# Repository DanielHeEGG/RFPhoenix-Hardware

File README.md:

# RF Phoenix
Open source wireless igniter for amateur rocketry

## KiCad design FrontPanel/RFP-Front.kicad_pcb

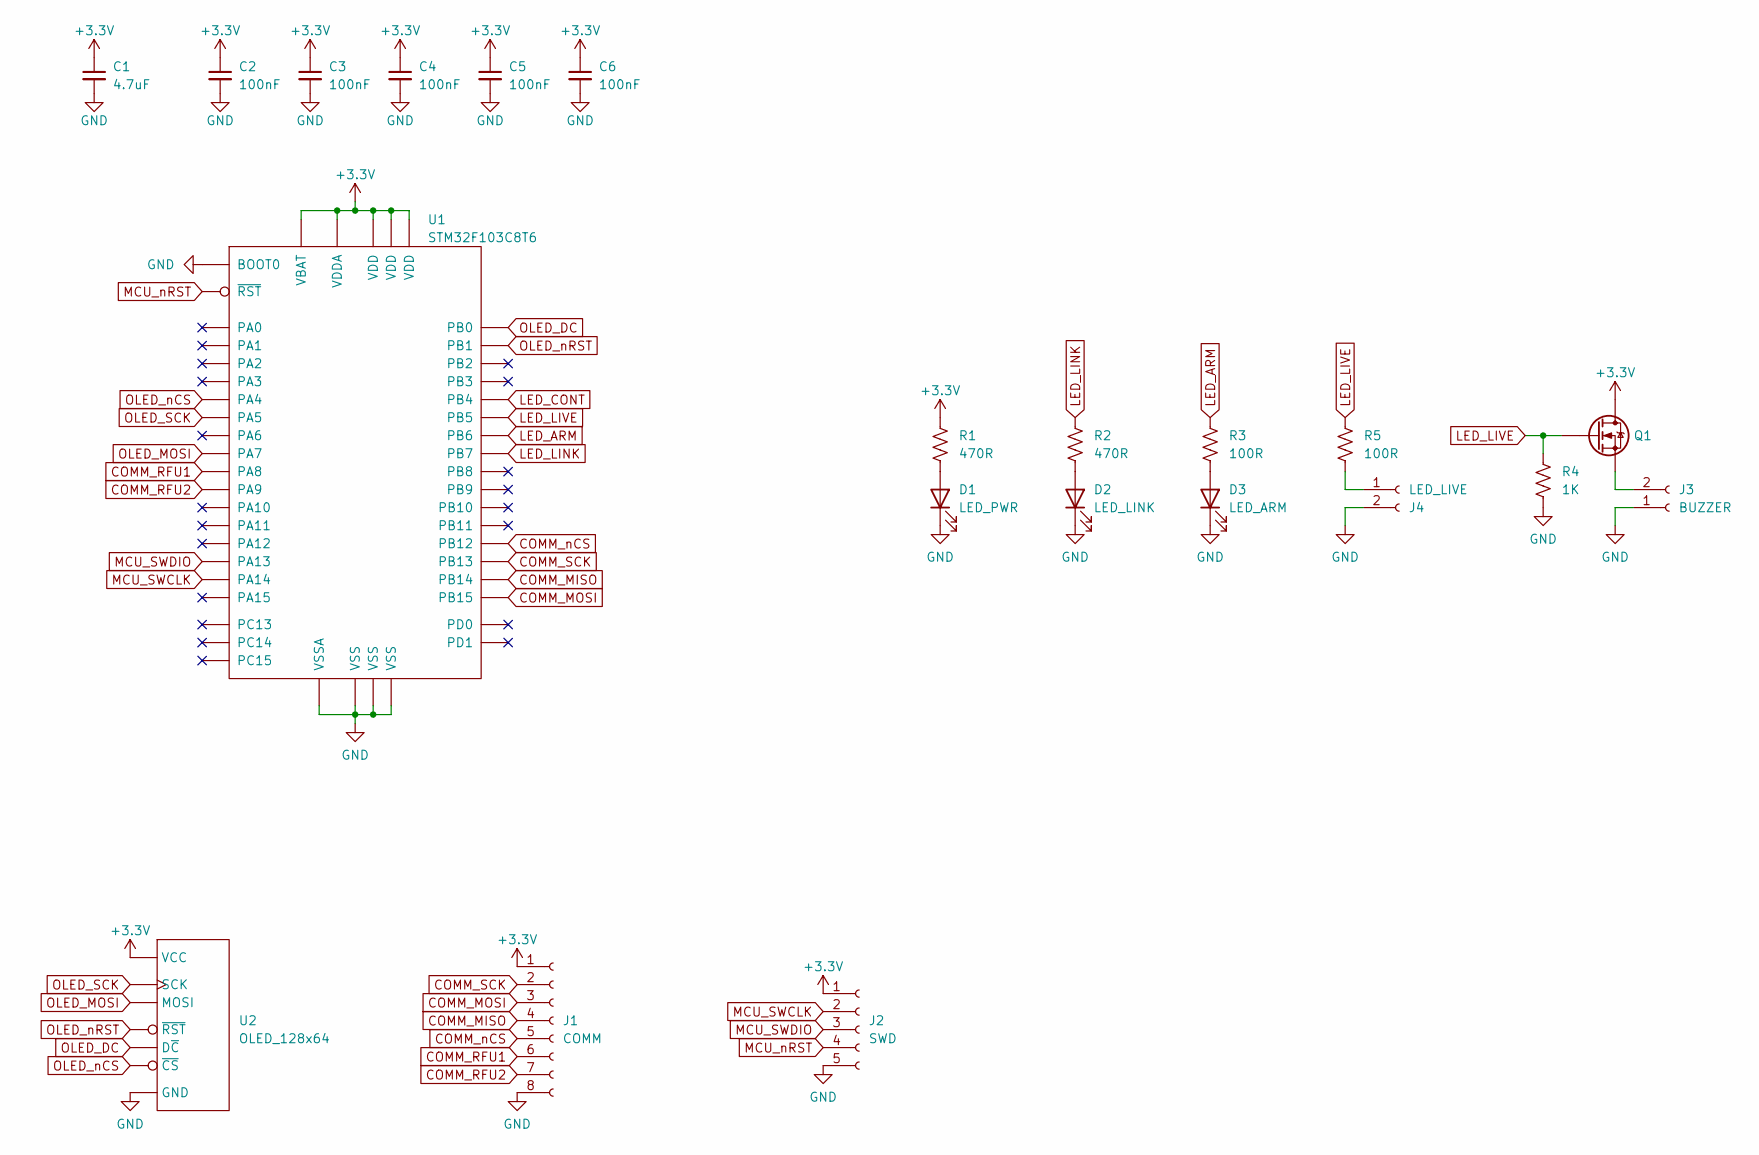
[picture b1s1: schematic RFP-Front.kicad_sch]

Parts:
C1: 4.7uF; C_0603_1608Metric; Part# Generic 4.7uF 6.3V 0603 X7R MLCC
C2, C3, C4, C5, C6: 100nF; C_0402_1005Metric; Part# Generic 100nF 6.3V 0402 X7R MLCC
D1: LED_PWR; LED_0603_1608Metric; Part# Generic Red 0603 LED
D2: LED_LINK; LED_0603_1608Metric; Part# Generic Green 0603 LED
D3: LED_ARM; LED_0603_1608Metric; Part# Generic Red 0603 LED
J1: COMM; Hirose_DF52-8S-0.8H_1x08-1MP_P0.80mm_Horizontal; Part# DF52-8S-0.8H
J2: SWD; Hirose_DF52-5S-0.8H_1x05-1MP_P0.80mm_Horizontal; Part# DF52-5S-0.8H
J3: BUZZER; Buzzer_Murata_PKMCS0909E
J4: LED_LIVE; R_2512_6332Metric
Q1: SOT-23; Part# Generic SOT-23 N-MOSFET
R1, R2: 470R; R_0402_1005Metric; Part# Generic 470R 0402 Resistor
R3, R5: 100R; R_0402_1005Metric; Part# Generic 100R 0402 Resistor
R4: 1K; R_0402_1005Metric; Part# Generic 1K 0402 Resistor
U1: STM32F103C8T6; LQFP-48_7x7mm_P0.5mm; Part# STM32F103C8T6
U2: OLED_128x64

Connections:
+3.3V: C1.1, C2.1, C3.1, C4.1, C5.1, C6.1, J1.1, J2.1, Q1.3 (D), R1.1, U1.1 (VBAT), U1.9 (VDDA), U1.24 (VDD), U1.36 (VDD), U1.48 (VDD), U2.2 (VCC)
COMM_MISO: J1.4, U1.27 (PB14)
COMM_MOSI: J1.3, U1.28 (PB15)
COMM_RFU1: J1.6, U1.29 (PA8)
COMM_RFU2: J1.7, U1.30 (PA9)
COMM_SCK: J1.2, U1.26 (PB13)
COMM_nCS: J1.5, U1.25 (PB12)
GND: C1.2, C2.2, C3.2, C4.2, C5.2, C6.2, D1.1 (K), D2.1 (K), D3.1 (K), J1.8, J2.5, J3.1, J4.2, R4.2, U1.8 (VSSA), U1.23 (VSS), U1.35 (VSS), U1.44 (BOOT0), U1.47 (VSS), U2.1 (GND)
LED_ARM: R3.1, U1.42 (PB6)
LED_CONT: U1.40 (PB4)
LED_LINK: R2.1, U1.43 (PB7)
LED_LIVE: Q1.1 (G), R4.1, R5.1, U1.41 (PB5)
MCU_SWCLK: J2.2, U1.37 (PA14)
MCU_SWDIO: J2.3, U1.34 (PA13)
MCU_nRST: J2.4, U1.7 (~RST)
unnamed: D1.2 (A), R1.2
unnamed: D2.2 (A), R2.2
unnamed: D3.2 (A), R3.2
unnamed: J3.2, Q1.2 (S)
unnamed: J4.1, R5.2
OLED_DC: U1.18 (PB0), U2.6 (D~C)
OLED_MOSI: U1.17 (PA7), U2.4 (MOSI)
OLED_SCK: U1.15 (PA5), U2.3 (SCK)
OLED_nCS: U1.14 (PA4), U2.7 (~CS)
OLED_nRST: U1.19 (PB1), U2.5 (~RST)

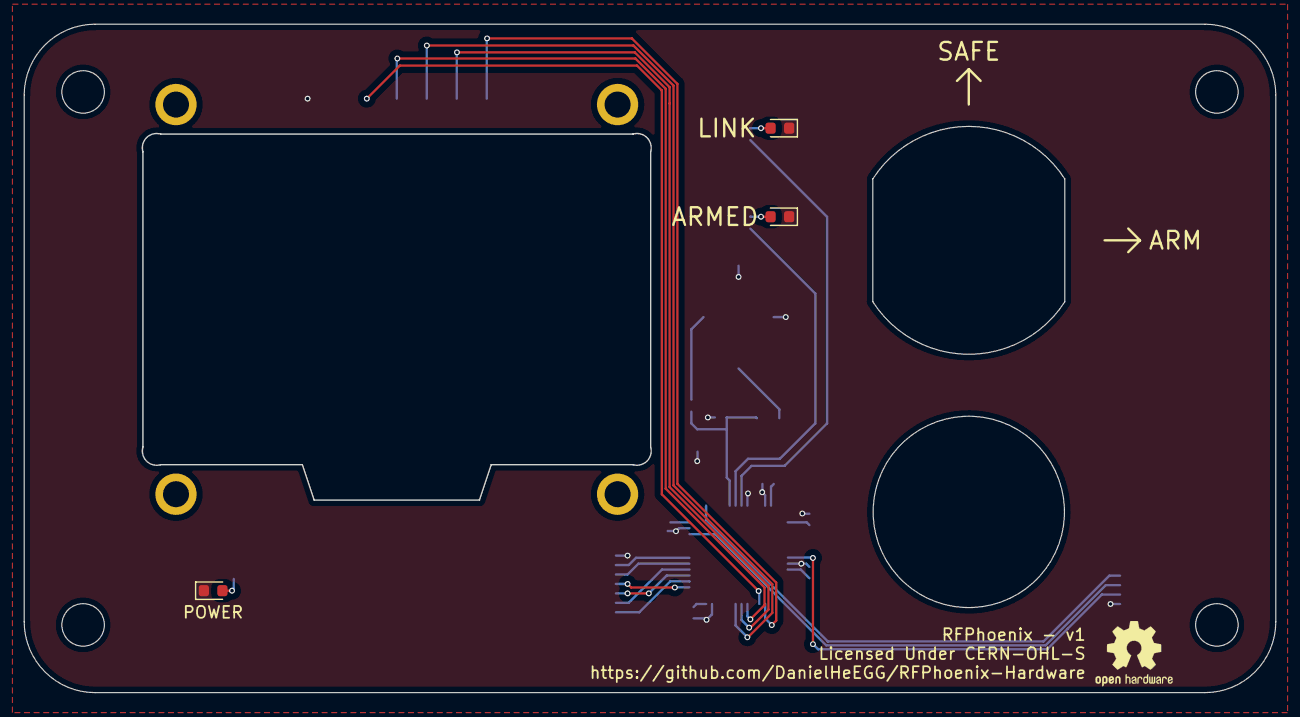
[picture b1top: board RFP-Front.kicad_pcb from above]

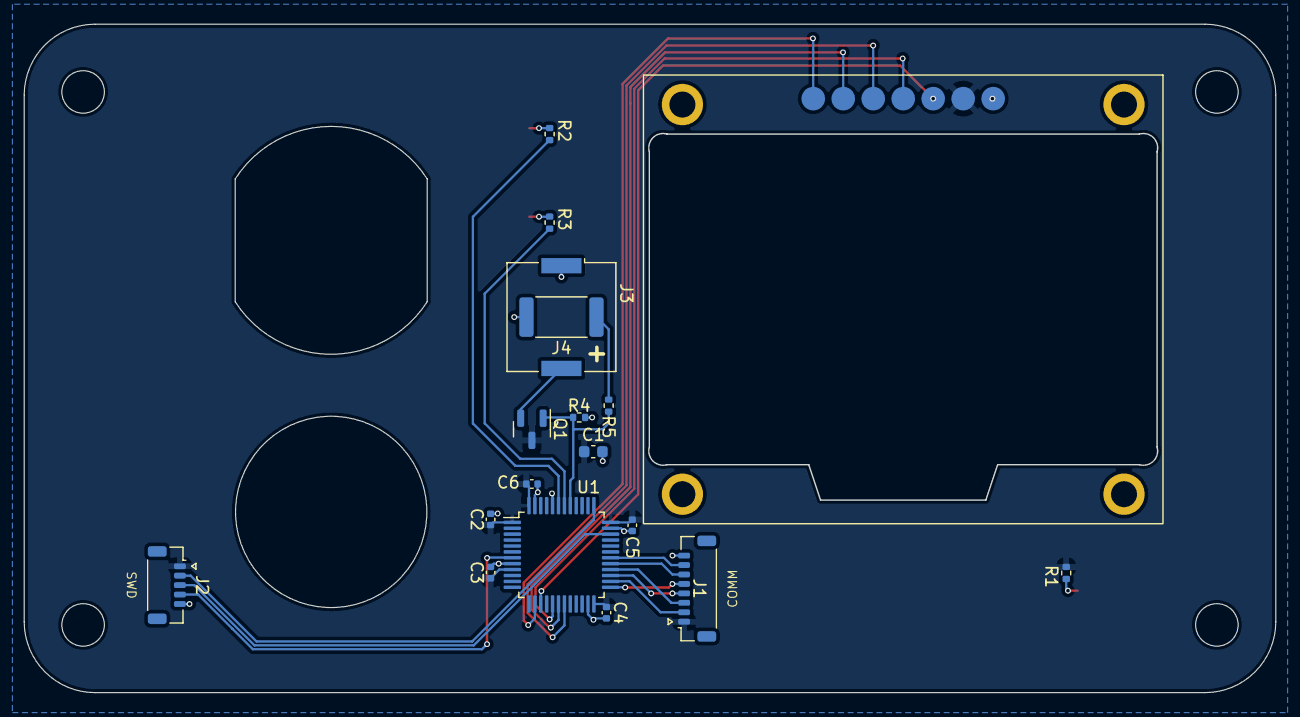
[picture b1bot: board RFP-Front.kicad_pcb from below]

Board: 2 copper layers, 106.0 x 56.6 mm, 21 parts (17 on the bottom side), 24 nets.

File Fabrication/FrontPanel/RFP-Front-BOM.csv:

"Qty","Designator","Comment","Footprint","Manufacturer","Part#","LCSC"
"1","C1","4.7uF","Capacitor_SMD:C_0603_1608Metric","Generic","Generic 4.7uF 6.3V 0603 X7R MLCC"
"5","C2, C3, C4, C5, C6","100nF","Capacitor_SMD:C_0402_1005Metric","Generic","Generic 100nF 6.3V 0402 X7R MLCC"
"1","D1","LED_PWR","LED_SMD:LED_0603_1608Metric","Generic","Generic Red 0603 LED","C2286"
"1","D2","LED_LINK","LED_SMD:LED_0603_1608Metric","Generic","Generic Green 0603 LED","C72043"
"1","D3","LED_ARM","LED_SMD:LED_0603_1608Metric","Generic","Generic Red 0603 LED","C2286"
"1","J1","DF52-8S-0.8H","Connector_Hirose:Hirose_DF52-8S-0.8H_1x08-1MP_P0.80mm_Horizontal","Hirose","DF52-8S-0.8H","C506726"
"1","J2","DF52-5S-0.8H","Connector_Hirose:Hirose_DF52-5S-0.8H_1x05-1MP_P0.80mm_Horizontal","Hirose","DF52-5S-0.8H","C597949"
"1","Q1","~","Package_TO_SOT_SMD:SOT-23","Generic","Generic SOT-23 N-MOSFET","C347475"
"2","R1, R2","470R","Resistor_SMD:R_0402_1005Metric","Generic","Generic 470R 0402 Resistor"
"2","R3, R5","100R","Resistor_SMD:R_0402_1005Metric","Generic","Generic 100R 0402 Resistor"
"1","R4","1K","Resistor_SMD:R_0402_1005Metric","Generic","Generic 1K 0402 Resistor"
"1","U1","STM32F103C8T6","Package_QFP:LQFP-48_7x7mm_P0.5mm","ST","STM32F103C8T6"

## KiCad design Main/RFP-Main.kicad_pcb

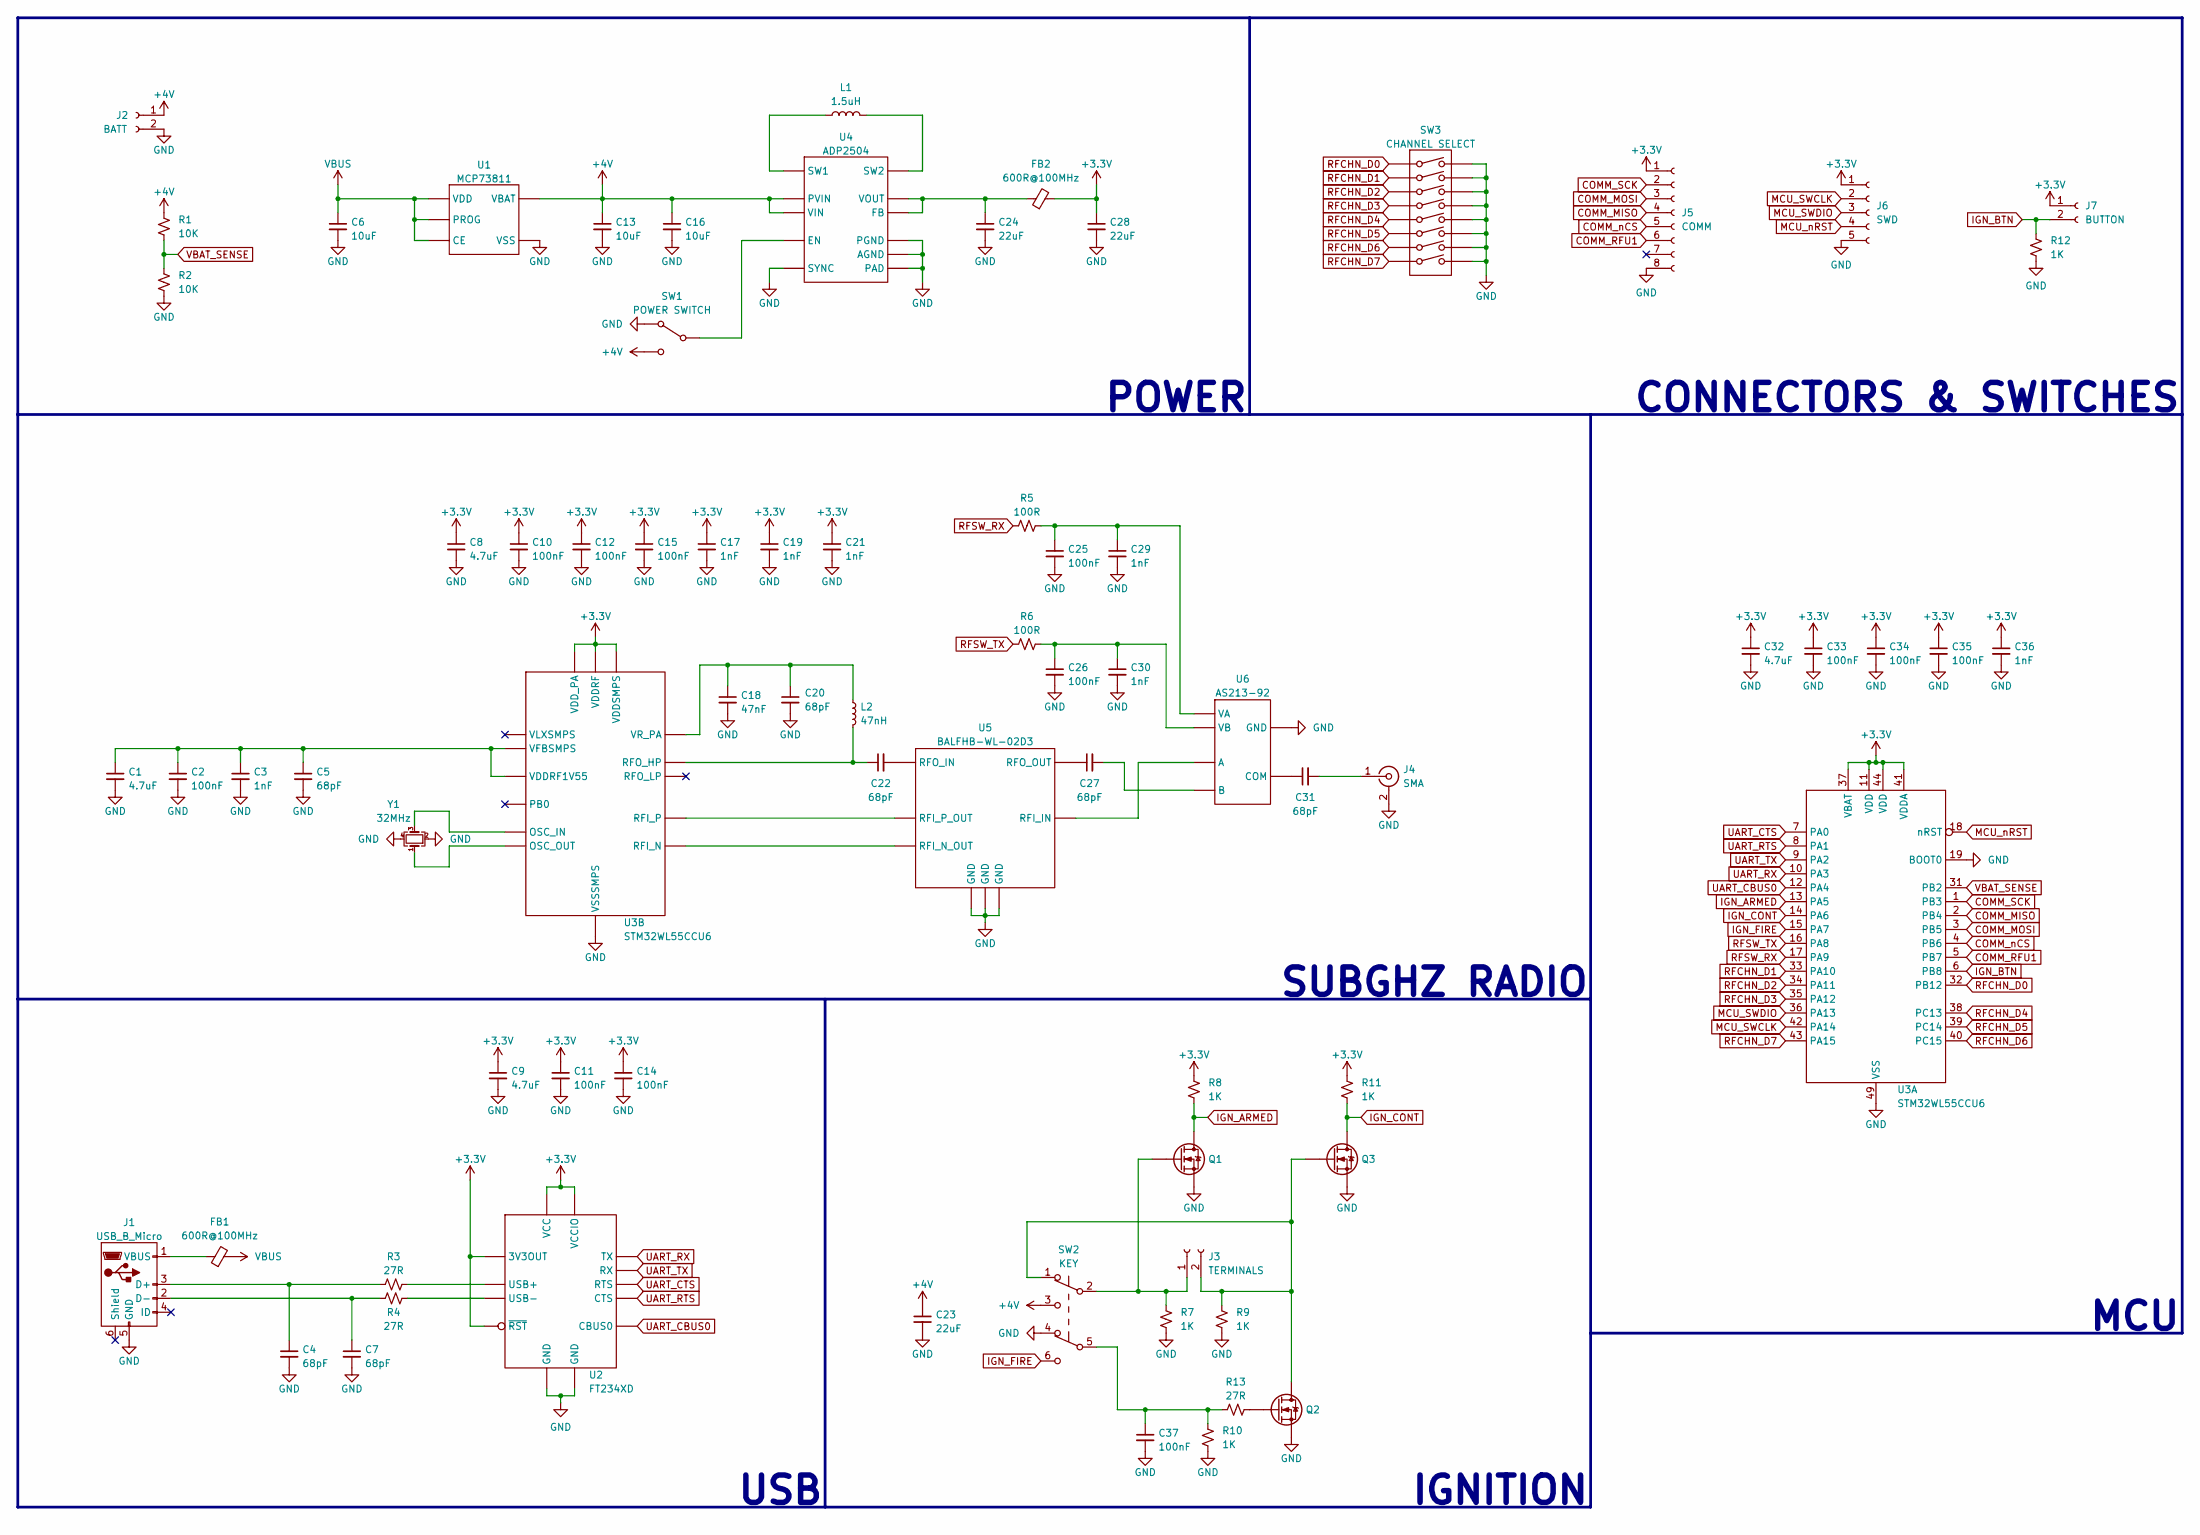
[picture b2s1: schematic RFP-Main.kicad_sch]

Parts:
C1, C8, C9, C32: 4.7uF; C_0603_1608Metric; Part# Generic 4.7uF 6.3V 0603 X7R MLCC
C2, C10, C11, C12, C14, C15, C25, C26, C33, C34, C35, C37: 100nF; C_0402_1005Metric; Part# Generic 100nF 6.3V 0402 X7R MLCC
C3, C17, C19, C21, C29, C30, C36: 1nF; C_0201_0603Metric; Part# Generic 1nF 6.3V 0201 X7R MLCC
C4, C5, C7, C20, C22, C27, C31: 68pF; C_0201_0603Metric; Part# GRM0335C1H680JA01D
C6, C13, C16: 10uF; C_0805_2012Metric; Part# Generic 10uF 6.3V 0805 X7R MLCC
C18: 47nF; C_0402_1005Metric; Part# Generic 47nF 6.3V 0402 X7R MLCC
C23, C24, C28: 22uF; C_0805_2012Metric; Part# Generic 22uF 6.3V 0805 X7R MLCC
FB1, FB2: 600R@100MHz; R_1206_3216Metric; Part# MH3261-601Y
J1: USB_B_Micro; USB_Micro-B_Molex-105017-0001; Part# 1050170001
J2: BATT; PinSocket_1x02_P2.54mm_Vertical
J3: TERMINALS; PinSocket_1x02_P2.54mm_Vertical
J4: SMA; SMA_Molex_73251-2200_Horizontal; Part# 0732512200
J5: COMM; Hirose_DF52-8S-0.8H_1x08-1MP_P0.80mm_Horizontal; Part# DF52-8S-0.8H
J6: SWD; Hirose_DF52-5S-0.8H_1x05-1MP_P0.80mm_Horizontal; Part# DF52-5S-0.8H
J7: BUTTON; PinSocket_1x02_P2.54mm_Vertical
L1: 1.5uH; L_1008_2520Metric; Part# LQM2HPN1R5MG0L
L2: 47nH; L_0402_1005Metric; Part# LQW15AN47NG00D
Q1, Q2, Q3: SOT-523; Part# DMG1012T
R1, R2: 10K; R_0402_1005Metric; Part# Generic 10K 0.1% 0402 Resistor
R3, R4, R13: 27R; R_0201_0603Metric; Part# Generic 27R 0201 Resistor
R5, R6: 100R; R_0402_1005Metric; Part# Generic 100R 0402 Resistor
R7, R8, R9, R10, R11, R12: 1K; R_0402_1005Metric; Part# Generic 1K 0402 Resistor
SW1: POWER SWITCH; SW_E-Switch_EG1224_SPDT_Angled; Part# EG1224
SW2: KEY; PinSocket_1x06_P2.54mm_Vertical
SW3: CHANNEL SELECT; SW_DIP_SPSTx08_Slide_6.7x21.88mm_W6.73mm_P2.54mm_LowProfile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; Part# 219-8LPSTR
U1: MCP73811; SOT-23-5; Part# MCP73811T-420I/OT
U2: FT234XD; DFN-12-1EP_3x3mm_P0.5mm_EP1.6x2.5mm; Part# FT234XD-R
U3: STM32WL55CCU6; QFN-48-1EP_7x7mm_P0.5mm_EP5.6x5.6mm; Part# STM32WL55CCU6
U4: ADP2504; LFCSP-WD-10-1EP_3x3mm_P0.5mm_EP1.64x2.38mm; Part# ADP2504ACPZ-3.3-R7
U5: BALFHB-WL-02D3; ST_CSPG-8; Part# BALFHB-WL-02D3
U6: AS213-92; SOT-363_SC-70-6; Part# AS213-92LF
Y1: 32MHz; Crystal_SMD_2016-4Pin_2.0x1.6mm; Part# NX2016SA-32M-EXS00A-CS06465

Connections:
+3.3V: C8.1, C9.1, C10.1, C11.1, C12.1, C14.1, C15.1, C17.1, C19.1, C21.1, C28.1, C32.1, C33.1, C34.1, C35.1, C36.1, FB2.2, J5.1, J6.1, J7.1, R8.1, R11.1, U2.2 (~RST), U2.3 (3V3OUT), U2.4 (VCC), U2.9 (VCCIO), U3.11 (VDD), U3.25 (VDD_PA), U3.28 (VDDRF), U3.37 (VBAT), U3.41 (VDDA), U3.44 (VDD), U3.46 (VDDSMPS)
+4V: C13.1, C16.1, C23.1, J2.1, R1.1, SW1.3 (C), SW2.3 (C), U1.3 (VBAT), U4.5 (PVIN), U4.8 (VIN)
COMM_MISO: J5.4, U3.2 (PB4)
COMM_MOSI: J5.3, U3.3 (PB5)
COMM_RFU1: J5.6, U3.5 (PB7)
COMM_SCK: J5.2, U3.1 (PB3)
COMM_nCS: J5.5, U3.4 (PB6)
GND: C1.2, C2.2, C3.2, C4.2, C5.2, C6.2, C7.2, C8.2, C9.2, C10.2, C11.2, C12.2, C13.2, C14.2, C15.2, C16.2, C17.2, C18.2, C19.2, C20.2, C21.2, C23.2, C24.2, C25.2, C26.2, C28.2, C29.2, C30.2, C32.2, C33.2, C34.2, C35.2, C36.2, C37.2, J1.5 (GND), J2.2, J4.2 (Ext), J5.8, J6.5, Q1.2 (S), Q2.2 (S), Q3.2 (S), R2.2, R7.2, R9.2, R10.2, R12.2, SW1.1 (A), SW2.4 (A), SW3.9, SW3.10, SW3.11, SW3.12, SW3.13, SW3.14, SW3.15, SW3.16, U1.2 (VSS), U2.5 (GND), U2.13 (GND), U3.19 (BOOT0), U3.48 (VSSSMPS), U3.49 (VSS), U4.3 (PGND), U4.7 (SYNC), U4.9 (AGND), U4.11 (PAD), U5.B1 (GND), U5.B2 (GND), U5.C2 (GND), U6.2 (GND), Y1.2, Y1.4
IGN_ARMED: Q1.3 (D), R8.2, U3.13 (PA5)
IGN_BTN: J7.2, R12.1, U3.6 (PB8)
IGN_CONT: Q3.3 (D), R11.2, U3.14 (PA6)
IGN_FIRE: SW2.6 (C), U3.15 (PA7)
MCU_SWCLK: J6.2, U3.42 (PA14)
MCU_SWDIO: J6.3, U3.36 (PA13)
MCU_nRST: J6.4, U3.18 (nRST)
unnamed: C1.1, C2.1, C3.1, C5.1, U3.29 (VDDRF1V55), U3.45 (VFBSMPS)
unnamed: C4.1, J1.3 (D+), R3.1
unnamed: C7.1, J1.2 (D-), R4.1
unnamed: C18.1, C20.1, L2.1, U3.24 (VR_PA)
unnamed: C22.1, L2.2, U3.23 (RFO_HP)
unnamed: C22.2, U5.A1 (RFO_IN)
unnamed: C24.1, FB2.1, U4.1 (VOUT), U4.10 (FB)
unnamed: C25.1, C29.1, R5.2, U6.4 (VA)
unnamed: C26.1, C30.1, R6.2, U6.6 (VB)
unnamed: C27.1, U5.C1 (RFO_OUT)
unnamed: C27.2, U6.1 (B)
unnamed: C31.1, U6.5 (COM)
unnamed: C31.2, J4.1 (In)
unnamed: FB1.1, J1.1 (VBUS)
unnamed: J3.1, Q1.1 (G), R7.1, SW2.2 (B)
unnamed: J3.2, Q2.3 (D), Q3.1 (G), R9.1, SW2.1 (A)
unnamed: L1.1, U4.4 (SW1)
unnamed: L1.2, U4.2 (SW2)
unnamed: Q2.1 (G), R13.2
unnamed: R3.2, U2.12 (USB+)
unnamed: R4.2, U2.1 (USB-)
unnamed: C37.1, R10.1, R13.1, SW2.5 (B)
unnamed: SW1.2 (B), U4.6 (EN)
unnamed: U3.20 (RFI_P), U5.A3 (RFI_P_OUT)
unnamed: U3.21 (RFI_N), U5.A2 (RFI_N_OUT)
unnamed: U3.26 (OSC_IN), Y1.3
unnamed: U3.27 (OSC_OUT), Y1.1
unnamed: U5.C3 (RFI_IN), U6.3 (A)
RFCHN_D0: SW3.1, U3.32 (PB12)
RFCHN_D1: SW3.2, U3.33 (PA10)
RFCHN_D2: SW3.3, U3.34 (PA11)
RFCHN_D3: SW3.4, U3.35 (PA12)
RFCHN_D4: SW3.5, U3.38 (PC13)
RFCHN_D5: SW3.6, U3.39 (PC14)
RFCHN_D6: SW3.7, U3.40 (PC15)
RFCHN_D7: SW3.8, U3.43 (PA15)
RFSW_RX: R5.1, U3.17 (PA9)
RFSW_TX: R6.1, U3.16 (PA8)
UART_CBUS0: U2.6 (CBUS0), U3.12 (PA4)
UART_CTS: U2.8 (RTS), U3.7 (PA0)
UART_RTS: U2.11 (CTS), U3.8 (PA1)
UART_RX: U2.7 (TX), U3.10 (PA3)
UART_TX: U2.10 (RX), U3.9 (PA2)
VBAT_SENSE: R1.2, R2.1, U3.31 (PB2)
VBUS: C6.1, FB1.2, U1.1 (CE), U1.4 (VDD), U1.5 (PROG)

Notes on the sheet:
IGNITION
CONNECTORS & SWITCHES
SUBGHZ RADIO
POWER
USB
MCU

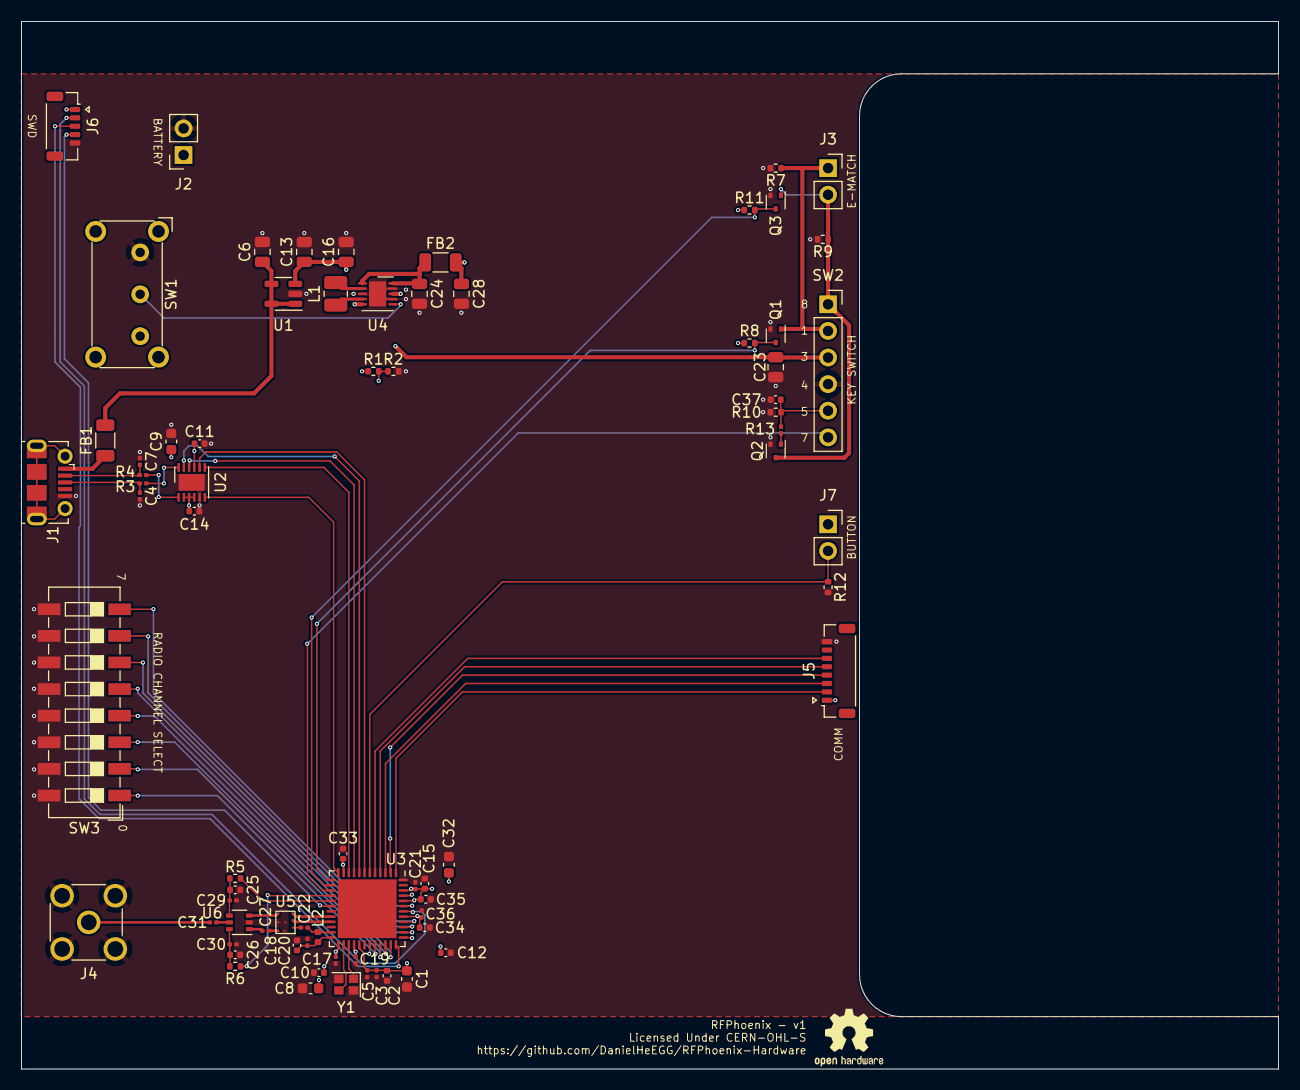
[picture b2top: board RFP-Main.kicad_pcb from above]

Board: 4 copper layers, 120.0 x 100.0 mm, 74 parts (0 on the bottom side), 60 nets.

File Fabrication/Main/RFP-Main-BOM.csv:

"Qty","Designator","Comment","Footprint","Manufacturer","Part#"
"4","C1, C8, C9, C32","4.7uF","Capacitor_SMD:C_0603_1608Metric","Generic","Generic 4.7uF 6.3V 0603 X7R MLCC"
"12","C2, C10, C11, C12, C14, C15, C25, C26, C33, C34, C35, C37","100nF","Capacitor_SMD:C_0402_1005Metric","Generic","Generic 100nF 6.3V 0402 X7R MLCC"
"7","C3, C17, C19, C21, C29, C30, C36","1nF","Capacitor_SMD:C_0201_0603Metric","Generic","Generic 1nF 6.3V 0201 X7R MLCC"
"7","C4, C5, C7, C20, C22, C27, C31","68pF","Capacitor_SMD:C_0201_0603Metric","Murata","GRM0335C1H680JA01D"
"3","C6, C13, C16","10uF","Capacitor_SMD:C_0805_2012Metric","Generic","Generic 10uF 6.3V 0805 X7R MLCC"
"1","C18","47nF","Capacitor_SMD:C_0402_1005Metric","Generic","Generic 47nF 6.3V 0402 X7R MLCC"
"3","C23, C24, C28","22uF","Capacitor_SMD:C_0805_2012Metric","Generic","Generic 22uF 6.3V 0805 X7R MLCC"
"2","FB1, FB2","600R@100MHz","Resistor_SMD:R_1206_3216Metric","Bourns","MH3261-601Y"
"1","J1","USB_B_Micro","Connector_USB:USB_Micro-B_Molex-105017-0001","Molex","1050170001"
"1","J4","SMA","Connector_Coaxial:SMA_Molex_73251-2200_Horizontal","Molex","0732512200"
"1","J5","COMM","Connector_Hirose:Hirose_DF52-8S-0.8H_1x08-1MP_P0.80mm_Horizontal","Hirose","DF52-8S-0.8H"
"1","J6","SWD","Connector_Hirose:Hirose_DF52-5S-0.8H_1x05-1MP_P0.80mm_Horizontal","Hirose","DF52-5S-0.8H"
"1","L1","1.5uH","Inductor_SMD:L_1008_2520Metric","Murata","LQM2HPN1R5MG0L"
"1","L2","47nH","Inductor_SMD:L_0402_1005Metric","Murata","LQW15AN47NG00D"
"3","Q1, Q2, Q3","~","Package_TO_SOT_SMD:SOT-523","Diodes","DMG1012T"
"2","R1, R2","10K","Resistor_SMD:R_0402_1005Metric","Generic","Generic 10K 0.1% 0402 Resistor"
"3","R3, R4, R13","27R","Resistor_SMD:R_0201_0603Metric","Generic","Generic 27R 0201 Resistor"
"2","R5, R6","100R","Resistor_SMD:R_0402_1005Metric","Generic","Generic 100R 0402 Resistor"
"6","R7, R8, R9, R10, R11, R12","1K","Resistor_SMD:R_0402_1005Metric","Generic","Generic 1K 0402 Resistor"
"1","SW1","POWER SWITCH","Button_Switch_THT:SW_E-Switch_EG1224_SPDT_Angled","E-Switch","EG1224"
"1","SW3","CHANNEL SELECT","Button_Switch_SMD:SW_DIP_SPSTx08_Slide_6.7x21.88mm_W6.73mm_P2.54mm_LowProfile_JPin","CTS","219-8LPSTR"
"1","U1","MCP73811","Package_TO_SOT_SMD:SOT-23-5","Microchip","MCP73811T-420I/OT"
"1","U2","FT234XD","Package_DFN_QFN:DFN-12-1EP_3x3mm_P0.5mm_EP1.6x2.5mm","FTDI","FT234XD-R"
"1","U3","STM32WL55CCU6","Package_DFN_QFN:QFN-48-1EP_7x7mm_P0.5mm_EP5.6x5.6mm","ST","STM32WL55CCU6"
"1","U4","ADP2504","Package_CSP:LFCSP-WD-10-1EP_3x3mm_P0.5mm_EP1.64x2.38mm","Analog","ADP2504ACPZ-3.3-R7"
"1","U5","BALFHB-WL-02D3","RFP-Footprints:ST_CSPG-8","ST","BALFHB-WL-02D3"
"1","U6","AS213-92","Package_TO_SOT_SMD:SOT-363_SC-70-6","Skyworks","AS213-92LF"
"1","Y1","32MHz","Crystal:Crystal_SMD_2016-4Pin_2.0x1.6mm","NDK","NX2016SA-32M-EXS00A-CS06465"

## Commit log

2023-04-10 Add front panel design & fabrication files
2023-04-13 Add main board design & fabrication files
2023-04-16 Add rear panel design & fabrication files
2023-05-20 Rearrange OLED and connector for front panel
2023-05-20 Rearrange and dim LEDs

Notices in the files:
FrontPanel/RFP-Front.kicad_pcb:
Licensed Under CERN-OHL-S
